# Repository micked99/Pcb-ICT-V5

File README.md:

# ICT-PCB-v2-v5
Eagle PCB for v2-v5 of "my" version of the ICT hab board
This pcb is made and setup for sw versions v2-v5 of the the ict code

ict_v361-xs // using the QFN/MLF version of the 328 - Verified working                                                                                
ict_v361 // using the TQFP version of the 328 - Verified working by Simonas LY2EN (@kareiva)

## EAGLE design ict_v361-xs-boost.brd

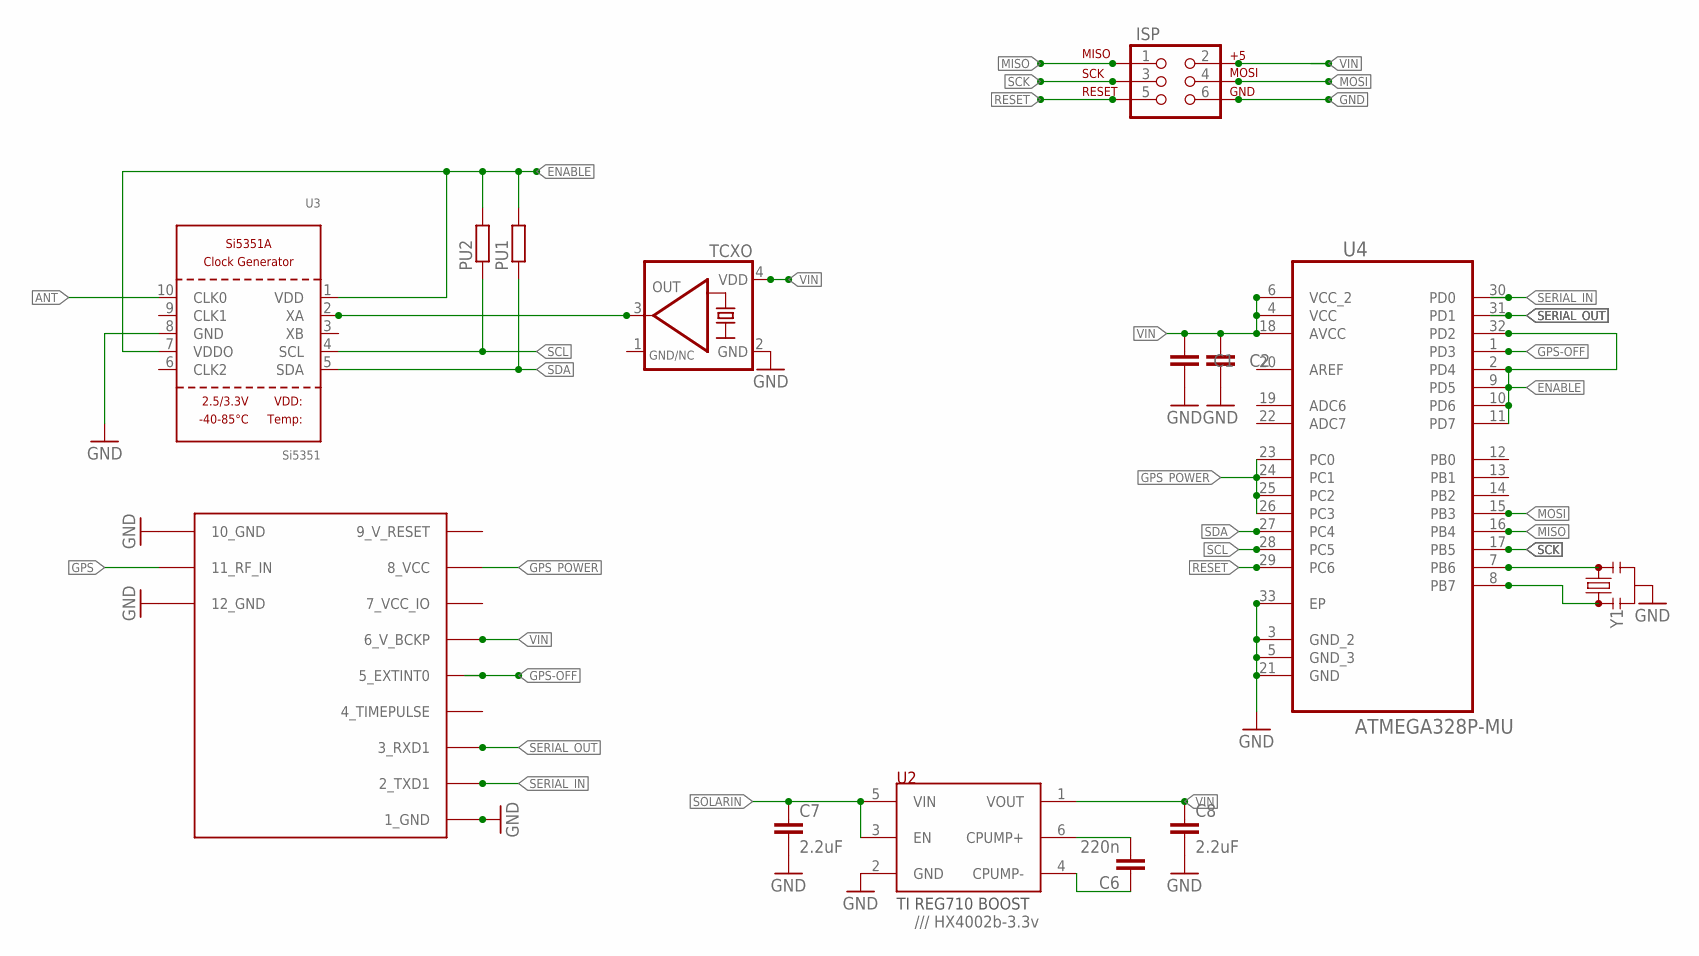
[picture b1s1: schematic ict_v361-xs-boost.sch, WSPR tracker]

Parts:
C1, C2: C-EUC0603K; C0603K
C6: 220n; 0603-CAP
C7, C8: 2.2uF; 0603-CAP
ISP: AVR_SPI_PRG_6PTH; 2X3
PU1, PU2: R-EU_R0603; R0603
TCXO: KXO-TCXO-CMOS-84; 3.2X2.5_KXO-84-TCXO
U2: /// HX4002b-3.3v; SOT-23-6L
U3: Si5351; MSOP10
U4: ATMEGA328P-MU; QFN50P500X500X100-33N
U$2: UBLOX_MAX
Y1: RESONATORSMD-4.5X2.0; RESONATOR-SMD-4.5X2.0

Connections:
7_VCC_IO: U$2.7_VCC_IO
9_V_RESET: U$2.9_V_RESET
ANT: U3.10 (CLK0)
ENABLE: PU1.2, PU2.2, U3.1 (VDD), U3.7 (VDDO), U4.2 (PD4), U4.9 (PD5), U4.10 (PD6), U4.11 (PD7), U4.32 (PD2)
GND: C1.2, C2.2, C7.2, C8.2, ISP.6, TCXO.2 (GND), U2.2 (GND), U3.8 (GND), U4.3 (GND_2), U4.5 (GND_3), U4.21 (GND), U4.33 (EP), U$2.1_GND, U$2.10_GND, U$2.12_GND, Y1.2
GND/NC: TCXO.1 (GND/NC)
GPS: U$2.11_RF_IN
GPS-OFF: U4.1 (PD3), U$2.5_EXTINT0
GPS_POWER: U4.23 (PC0), U4.24 (PC1), U4.25 (PC2), U4.26 (PC3), U$2.8_VCC
MISO: ISP.1, U4.16 (PB4)
MOSI: ISP.4, U4.15 (PB3)
unnamed: U4.7 (PB6), Y1.3
unnamed: U4.8 (PB7), Y1.1
unnamed: TCXO.3 (OUT), U3.2 (XA)
unnamed: C6.2, U2.6 (CPUMP+)
unnamed: C6.1, U2.4 (CPUMP-)
RESET: ISP.5, U4.29 (PC6)
SCK: ISP.3, U4.17 (PB5)
SCL: PU2.1, U3.4 (SCL), U4.28 (PC5)
SDA: PU1.1, U3.5 (SDA), U4.27 (PC4)
SERIAL_IN: U4.30 (PD0), U$2.2_TXD1
SERIAL_OUT: U4.31 (PD1), U$2.3_RXD1
SOLARIN: C7.1, U2.3 (EN), U2.5 (VIN)
VIN: C1.1, C2.1, C8.1, ISP.2, TCXO.4 (VDD), U2.1 (VOUT), U4.4 (VCC), U4.6 (VCC_2), U4.18 (AVCC), U$2.6_V_BCKP

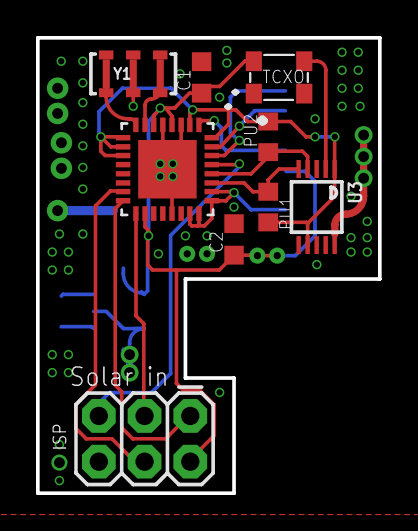
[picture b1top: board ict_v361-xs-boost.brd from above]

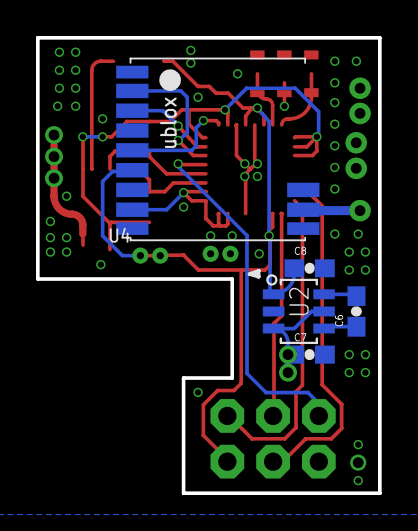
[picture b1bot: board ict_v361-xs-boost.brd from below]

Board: 2 copper layers, 19.0 x 25.3 mm, 14 parts (5 on the bottom side), 19 nets.

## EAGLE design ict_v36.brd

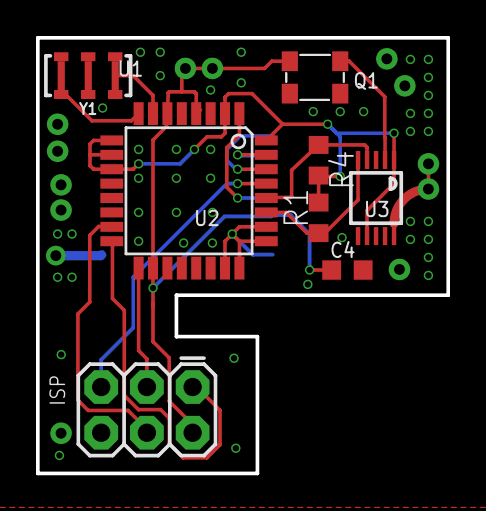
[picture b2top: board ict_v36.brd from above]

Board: 2 copper layers, 22.8 x 24.2 mm, 9 parts (1 on the bottom side), 16 nets.

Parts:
C4: 1uF 0603; C0603K
ISP: 2X3
Q1: 3.2X2.5_KXO-84-TCXO
R1, R4: R0603
U2: ATMEGA328P; TQFP32-08
U3: Si5351A-B-GT; MSOP10
U$2: UBLOX_MAX
Y1: RESONATOR-SMD-4.5X2.0

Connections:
ENABLE: R1.2, R4.2, U2.2, U2.9, U2.10, U2.11, U2.32, U3.1, U3.7
GND: C4.2, ISP.6, Q1.2, U2.3, U2.5, U2.21, U3.8, U$2.1_GND, U$2.10_GND, U$2.12_GND, Y1.2
GPS-OFF: U2.1, U$2.5_EXTINT0
GPS_ON_OFF: U2.23, U2.24, U2.25, U2.26, U$2.8_VCC
MISO: ISP.1, U2.16
MOSI: ISP.4, U2.15
unnamed: U2.8, Y1.3
unnamed: U2.7, Y1.1
unnamed: Q1.3, U3.2
RESET: ISP.5, U2.29
SCK: ISP.3, U2.17
SCL: R4.1, U2.28, U3.4
SDA: R1.1, U2.27, U3.5
SERIAL_IN: U2.30, U$2.2_TXD1
SERIAL_OUT: U2.31, U$2.3_RXD1
VIN: C4.1, ISP.2, Q1.4, U2.4, U2.6, U2.18, U$2.6_V_BCKP

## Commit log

2021-03-22 Verified the ict_v361 PCB
    Ordered a handful of PCB's based on the untested ict_v361 design.
    Parts used:
    * 3k9 resistors for pull-up
    * 8MHz internal clock
    * 27MHz TCXO
    * ATGM336H GPS
2021-07-31 Add files via upload
    incl REG710 / HX4002b Charge boost

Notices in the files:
parts and their libraries:
microbuilder: This work is placed in the public domain, and may be freely used for commercial and non-commercial work with the following conditions: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
crystal-geyer_V1_0: Copyright: Geyer-Electronic
